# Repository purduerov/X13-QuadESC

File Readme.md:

# Readme for X13-QuadESC

Whenever you make a new part, download the datasheet and save it here _**and**_ with the part in the parts library

Always pull other people's changes before beginning to work
`git pull`

Be sure to push your changes after  working on them. Run:
1. `git add .` to add any files in this directory or a subdirectory
or `git add -u` to add any modified files
2. (Optional) `git clean -nX` to see what ignored files can be removed
	`git clean -fX` removes ignored files (Eagle backups)
3. `git commit -m "helpful commit message"` with a description of the work that you did
4. `git push` to push your work to github

Other helpful commands
* `git status` says information about modified and staged files
* `git log` shows the recent commits of the repository
* `git log filename.extension` show the recent commits for just that file
* `git checkout first-couple-letter-of-commit-id` lets you go back to a previous version
* `git checkout master` brings you back to the latest commit
* `git tag` lists the tags
* `git tag -a orderX -m "the version of the board placed for the X'th order"` tag a specific commit
* `git push --tags` needed to push tags to remote
* `git show orderX` show the commit log for the given tag
* `git checkout orderX` go back and interact with the files at the tagged commit

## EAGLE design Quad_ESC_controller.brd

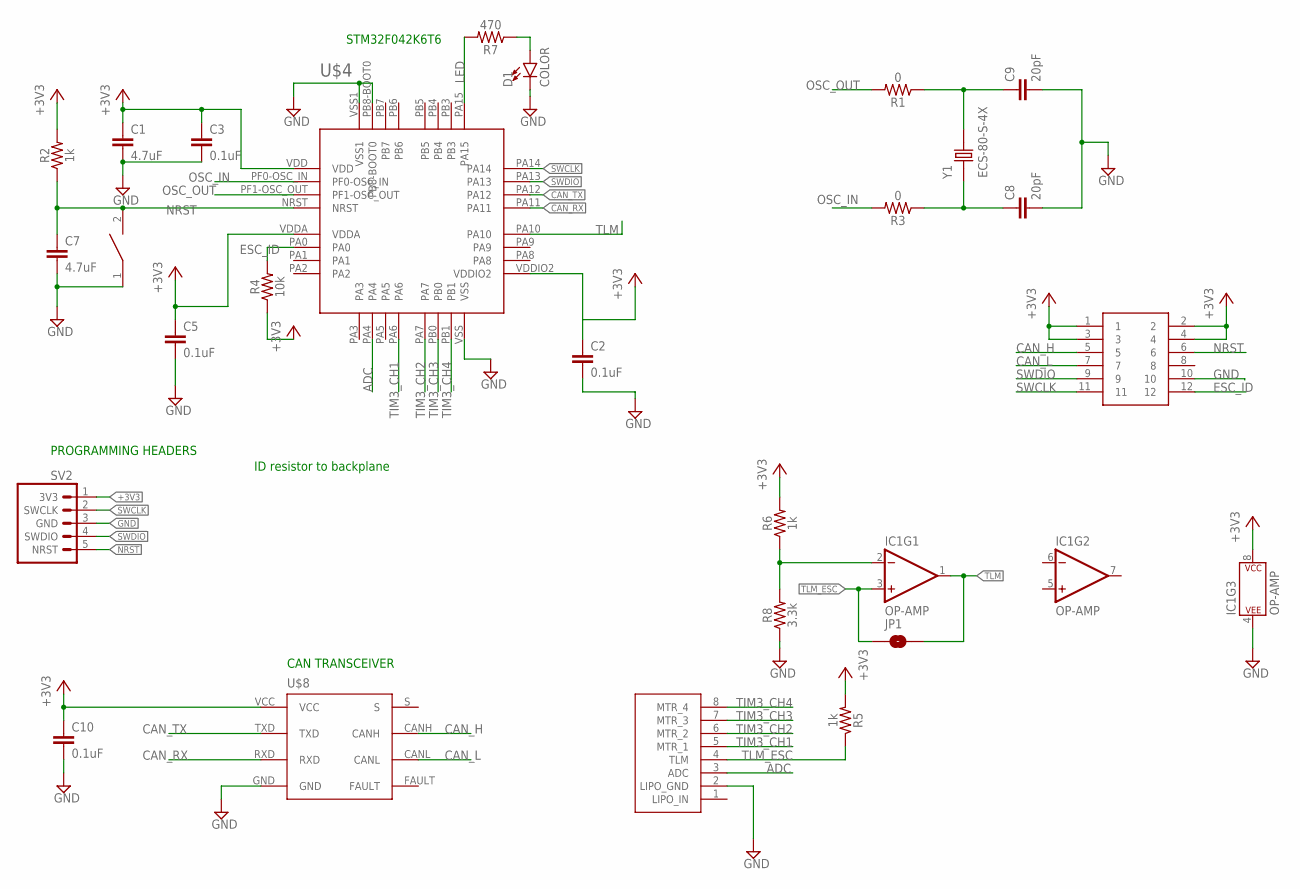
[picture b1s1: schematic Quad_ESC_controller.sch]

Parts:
C1, C7: 4.7uF; 0603
C2, C3, C5, C10: 0.1uF; 0603
C8, C9: 20pF; 0603
D1: COLOR; 0805
IC1: OP-AMP; SO08
JP1: JUMPER-SMT_2_NO_SILK; SMT-JUMPER_2_NO_SILK
R1, R3: 0; 0603
R2, R5, R6: 1k; 0603
R4: 10k; 0603
R7: 470; 0603
R8: 3.3k; 0603
RESET: DISCRETECOMPONENTS_SWITCH; DISCRETECOMPONENTS_SW_2512
SV2: 3V3 -SWCLK-GND-SWDIO- NRST; 1X05
U$2: JST-8PIN; 8PIN_CONNECTOR
U$3: BACKPLANE_CONNECTORSESC; BACKPLANE_CONNECTORS_ESC
U$4: STM32F042K6T6
U$8: TCAN337D
Y1: ECS-80-S-4X; XTAL_ECS-80-S-4X

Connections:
+3V3: C1.1, C2.1, C3.1, C5.1, C10.1, IC1.8 (P$V+), R2.2, R4.1, R5.2, R6.2, SV2.1 (3V3), U$3.1, U$3.2, U$3.3, U$3.4, U$4.VDD, U$4.VDDA, U$4.VDDIO2, U$8.VCC
ADC: U$2.3 (ADC), U$4.PA4
CAN_H: U$3.5, U$8.CANH
CAN_L: U$3.7, U$8.CANL
CAN_RX: U$4.PA11, U$8.RXD
CAN_TX: U$4.PA12, U$8.TXD
ESC_ID: R4.2, U$3.12, U$4.PA0
GND: C1.2, C2.2, C3.2, C5.2, C7.2, C8.2, C9.2, C10.2, D1.C, IC1.4 (P$V-), R8.1, RESET.1, SV2.3 (GND), U$2.2 (LIPO_GND), U$3.10, U$4.PB8-BOOT0, U$4.VSS, U$4.VSS1, U$8.GND
LED: R7.2, U$4.PA15
unnamed: C9.1, R1.1, Y1.2
unnamed: C8.1, R3.1, Y1.1
unnamed: IC1.2 (-IN), R6.1, R8.2
unnamed: D1.A, R7.1
NRST: C7.1, R2.1, RESET.2, SV2.5 (NRST), U$3.6, U$4.NRST
OSC_IN: R3.2, U$4.PF0-OSC_IN
OSC_OUT: R1.2, U$4.PF1-OSC_OUT
SWCLK: SV2.2 (SWCLK), U$3.11, U$4.PA14
SWDIO: SV2.4 (SWDIO), U$3.9, U$4.PA13
TIM3_CH1: U$2.5 (MTR_1), U$4.PA6
TIM3_CH2: U$2.6 (MTR_2), U$4.PA7
TIM3_CH3: U$2.7 (MTR_3), U$4.PB0
TIM3_CH4: U$2.8 (MTR_4), U$4.PB1
TLM: IC1.1 (OUT), JP1.2, U$4.PA10
TLM_ESC: IC1.3 (+IN), JP1.1, R5.1, U$2.4 (TLM)

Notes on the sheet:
STM32F042K6T6
PROGRAMMING HEADERS
CAN TRANSCEIVER
ID resistor to backplane

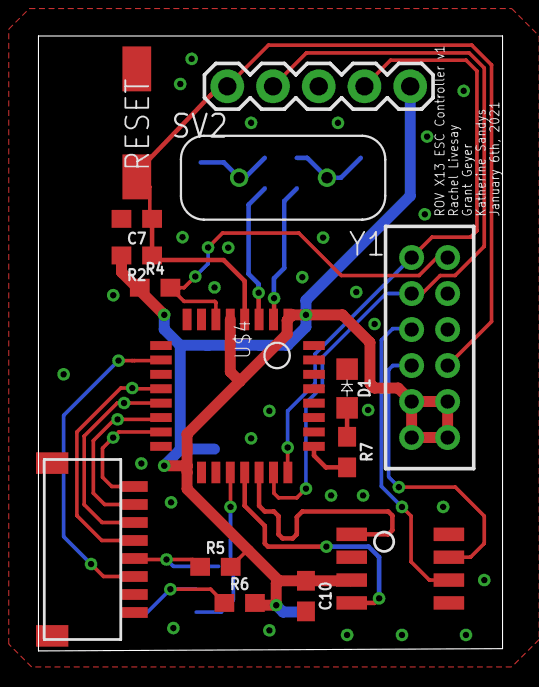
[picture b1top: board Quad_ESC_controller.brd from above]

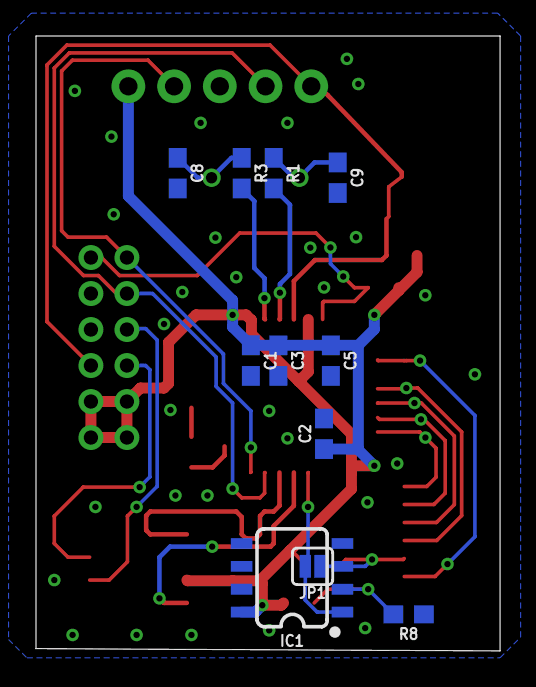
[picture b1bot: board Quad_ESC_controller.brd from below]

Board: 2 copper layers, 25.8 x 34.2 mm, 26 parts (11 on the bottom side), 24 nets.

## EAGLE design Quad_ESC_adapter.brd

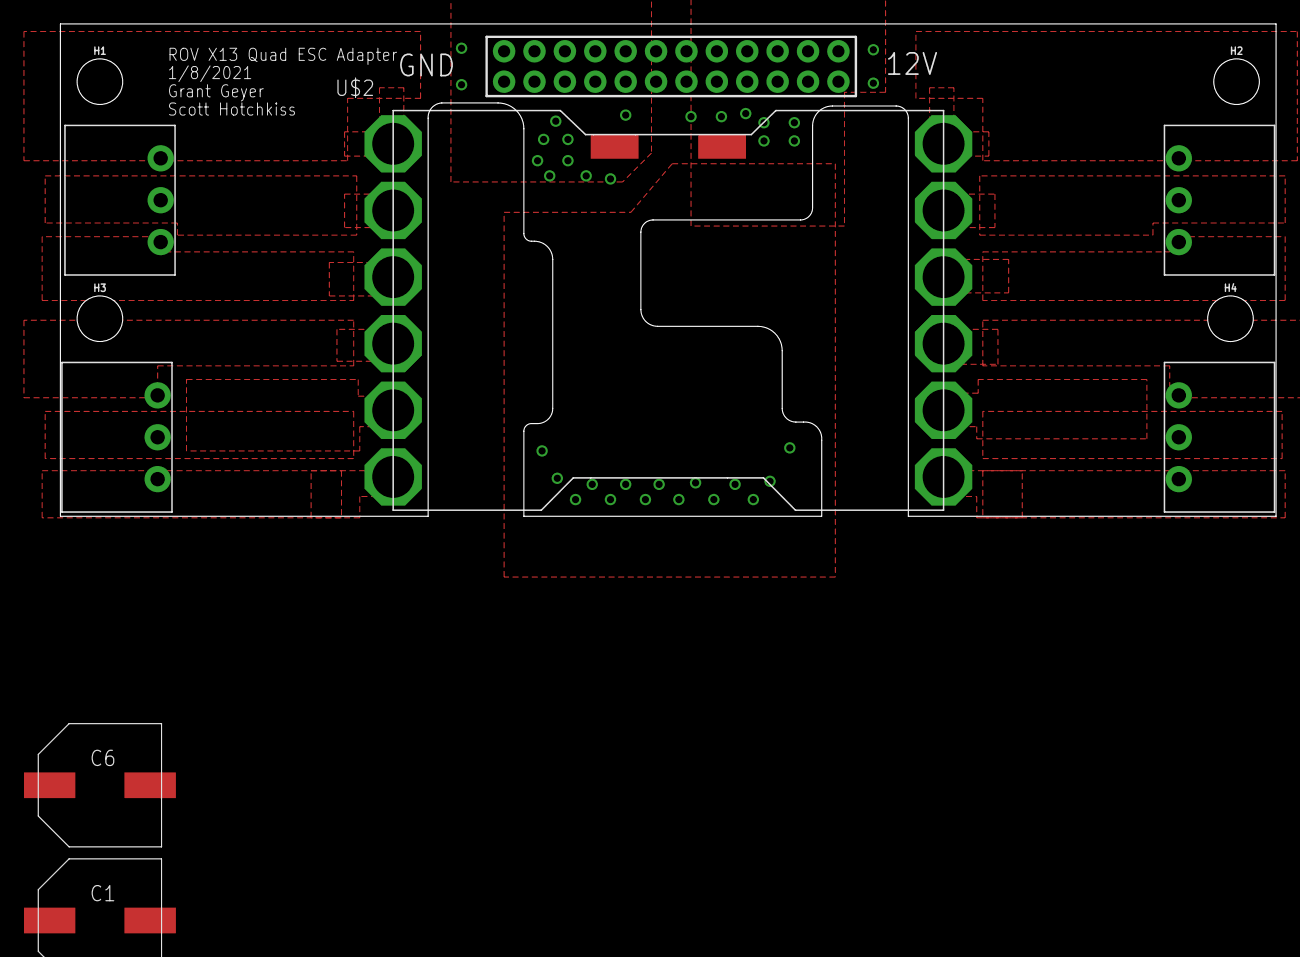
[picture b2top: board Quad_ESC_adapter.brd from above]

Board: 2 copper layers, 101.6 x 41.1 mm, 13 parts (1 on the bottom side), 14 nets, no tracks yet.

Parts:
C1, C5, C6: 330uF; CAPAE1030X1050N
H1, H2, H3, H4: 6-32-HOLE
J1, J2, J3, J4: 284512-3
U$2: BACKPLANE_ESC_ADAPTER_PWRESC; BACKPLANE_ESC_ADAPTER_ESC_PWR
U$10: LUMENIER_QUAD-NO-CUT

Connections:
12V: C1.+, C5.+, C6.+, U$2.12V@1, U$2.12V@2, U$2.12V@3, U$2.12V@4, U$2.12V@5, U$2.12V@6, U$2.12V@7, U$2.12V@8, U$2.12V@9, U$2.12V@10, U$2.12V@11, U$2.12V@12, U$10.VIN
ESC1_B: J1.3, U$10.1
ESC1_R: J1.1, U$10.3
ESC1_Y: J1.2, U$10.2
ESC2_B: J2.3, U$10.4
ESC2_R: J2.1, U$10.6
ESC2_Y: J2.2, U$10.5
ESC3_B: J3.1, U$10.12
ESC3_R: J3.3, U$10.10
ESC3_Y: J3.2, U$10.11
ESC4_B: J4.1, U$10.9
ESC4_R: J4.3, U$10.7
ESC4_Y: J4.2, U$10.8
GND: C1.-, C5.-, C6.-, U$2.GND@1, U$2.GND@2, U$2.GND@3, U$2.GND@4, U$2.GND@5, U$2.GND@6, U$2.GND@7, U$2.GND@8, U$2.GND@9, U$2.GND@10, U$2.GND@11, U$2.GND@12, U$10.GND

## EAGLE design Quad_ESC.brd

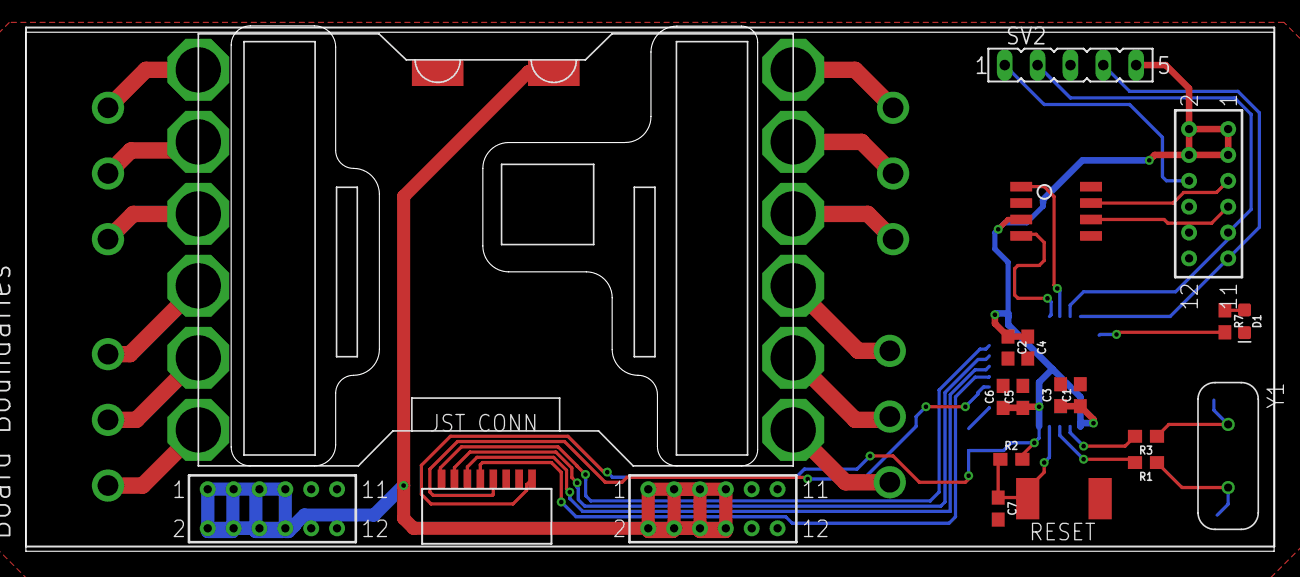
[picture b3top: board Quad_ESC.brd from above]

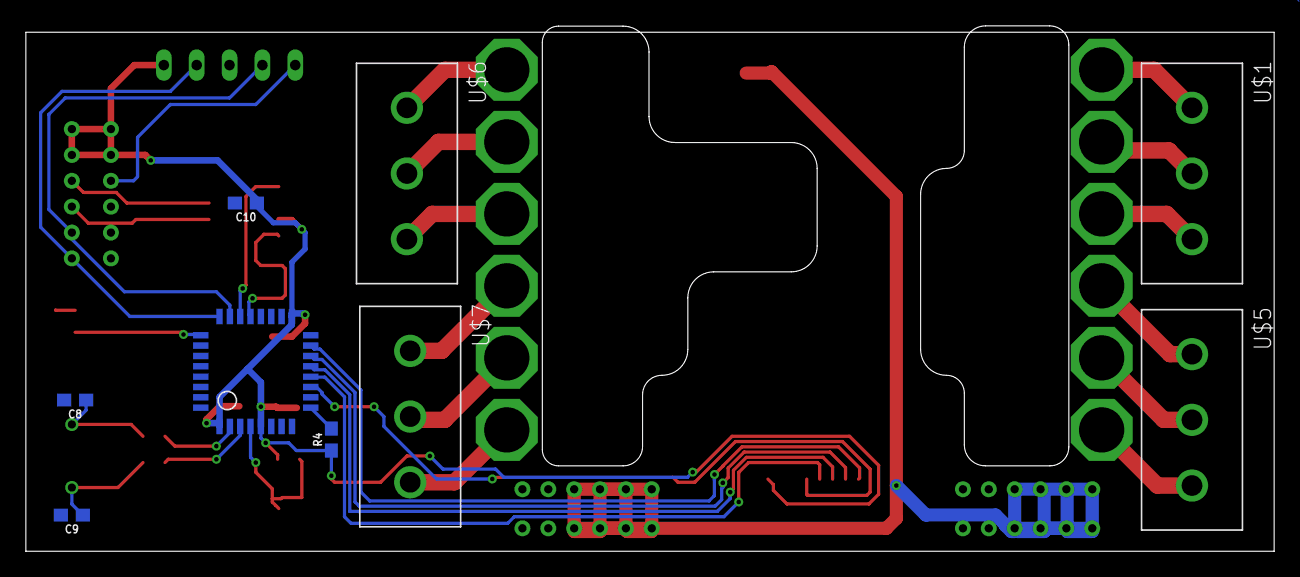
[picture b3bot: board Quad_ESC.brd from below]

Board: 2 copper layers, 96.5 x 40.1 mm, 28 parts (9 on the bottom side), 35 nets.

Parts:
C1, C2, C3, C4, C5, C6, C7, C8, C9: 4.7uF; 0603
C10: 100nF; 0603
D1: LED-0603
R1, R2, R3: 1k; 0603
R4: 10k; 0603
R7: 0603
RESET: SW_2512
SV2: FE05-1
U$1, U$5, U$6, U$7: 3PINCONNECTOR
U$2: 8PIN_CONNECTOR; 8PI_CONNECTOR
U$3: BACKPLANE_CONNECTORS
U$4: STM32F042K6T6
U$8: TCAN337D
U$10: LUMENIER_QUAD
Y1: ECS-80-S-4X; XTAL_ECS-80-S-4X

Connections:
+3V3: C1.1, C2.1, C3.1, C4.1, C5.1, C6.1, C10.1, R2.2, R4.1, SV2.5, U$2.P$1, U$3.25, U$3.26, U$3.27, U$3.28, U$4.VDD, U$4.VDDA, U$4.VDDIO2, U$8.VCC
+12V: U$3.1, U$3.2, U$3.3, U$3.4, U$3.5, U$3.6, U$3.7, U$3.8, U$3.13, U$3.14, U$3.15, U$3.16, U$3.17, U$3.18, U$3.19, U$3.20, U$10.VIN
CAN_H: U$3.29, U$8.CANH
CAN_L: U$3.31, U$8.CANL
CAN_RX: U$4.PA11, U$8.RXD
CAN_TX: U$4.PA12, U$8.TXD
ESC1_B: U$1.A, U$10.1
ESC1_R: U$1.C, U$10.3
ESC1_Y: U$1.B, U$10.2
ESC2_B: U$5.A, U$10.4
ESC2_R: U$5.C, U$10.6
ESC2_Y: U$5.B, U$10.5
ESC3_B: U$6.A, U$10.12
ESC3_R: U$6.C, U$10.10
ESC3_Y: U$6.B, U$10.11
ESC4_B: U$7.A, U$10.9
ESC4_R: U$7.C, U$10.7
ESC4_Y: U$7.B, U$10.8
GND: C1.2, C2.2, C3.2, C4.2, C5.2, C6.2, C7.2, C8.2, C9.2, C10.2, D1.C, RESET.1, SV2.3, U$2.P$2, U$2.P$3, U$3.9, U$3.10, U$3.11, U$3.12, U$3.21, U$3.22, U$3.23, U$3.24, U$4.PB8-BOOT0, U$4.VSS, U$4.VSS1, U$8.GND, U$10.GND
LED: R7.2, U$4.PA15
unnamed: C9.1, R1.1, Y1.2
unnamed: C8.1, R3.1, Y1.1
unnamed: R4.2, U$4.PA3
unnamed: D1.A, R7.1
NRST: SV2.1, U$3.30
NRST1: C7.1, R2.1, RESET.2, U$4.NRST
OSC_IN: R3.2, U$4.PF0-OSC_IN
OSC_OUT: R1.2, U$4.PF1-OSC_OUT
SWCLK: SV2.4, U$3.35, U$4.PA14
SWDIO: SV2.2, U$3.33, U$4.PA13
TIM3_CH1: U$2.P$5, U$4.PA6
TIM3_CH2: U$2.P$6, U$4.PA7
TIM3_CH3: U$2.P$7, U$4.PB0
TIM3_CH4: U$2.P$8, U$4.PB1
TLM: U$2.P$4, U$4.PA5

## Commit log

2020-09-18 setup of repo
2020-10-10 Create Quad_ESC.sch
    created file, moved over parts from X12 version
2020-10-17 Lib Changes/Schem Update
    Added Cutouts/changed dimensions of ESC footprint in library; added board parts to library; tweaked schematic; created board file.
2020-10-17 Lib Update (again)
    ok definitely did not push the wrong version of the library file last time haha
2020-10-17 Lib Update/Sch Update
    Migrated 3 pin connectors from X-11 AFRO lib; fixed BLHeli symbol so labels no longer overlap; fixed connections and placement on schematic.
2020-10-21 Board Update
    Added minor pin connections
2020-10-24 Lib/Schem Update
    tweaked connections to STM chip; split esc device into lumenier ESC and 8 pin connector (need to figure out how to pair those still :/ ); scooted around components on schematic
2020-10-25 turn off layer 93 (pins). Create correct dimension board
2020-10-27 made board a little smaller
2020-11-12 Schem/Lib Update
    added new footprint to schematic and library, added ID resistor to chip, standardized symbols across schematic
2020-11-14 Minor Sch Fixes/Board Placement
    Fixed issues with schematic and doubling of backplane connectors, precursory board placements and connections
2020-11-14 Quick Board Update
    ripup; done for presentation, only placement of components present on board
2020-11-21 Board/Schem Update
    added CLT low profile samtec connectors to schem/board, looking at the connector spacing on the board stresses me out ;-;
2020-11-21 Board Update
    actually put the connectors on the right side of the board this time haha
2020-12-02 Connector Update!!
    made new part for backplae connectors with proper spacing, updated schematic and board accordingly
2020-12-03 Update BLHeli_32 45A.lbr
    Added boundary box to connectors part for backplane.
2020-12-06 Connector Updates, Board Routing
    Backplane connectors updated, board routing on right side completed
2020-12-06 Signals fixed a bit?
2020-12-06 Board Update (again)
2020-12-06 Quick, Minor Changes
2021-01-03 remove lumenier and adjust size for controller
2021-01-03 split into adapter board
2021-01-04 complete connector placement
2021-01-05 Export step file
2021-01-06 Placement/Routing Update
    the board and sch are out of sync and i have no idea how they got that way h e l p
2021-01-06 tented vias under lumenier
2021-01-06 routed wider board
2021-01-07 Placement/Routing Update
    microcontroller movied to front, CAN signals length checked
2021-01-07 Small Board Change
    forgot to trace length check the OSC in/out oops
2021-01-07 Library Changes for Backplane :)
2021-01-07 Routing Update
    rerouted new connector into board :)
2021-01-07 Labels/Final Touches
    Added: Vias, Names/Date/Board Label, Kingsman Logo :D
2021-01-08 routed with 2x12 block. Basically ready to order
2021-01-09 single outline version
2021-01-09 this has been the best graphic in the history of graphics, maybe ever
2021-01-10 Final Board Changes ✽-(ˆ▿ˆ)/✽
    thank god
    (changes: vias con. to GND, esc id/tlm connections, design moved, connector footprint replaced, font sizes changed)
2021-01-10 JST part
2021-01-10 exports for ordering
2021-01-11 Final Board Changes Pt. 2: Electric Boogaloo
    Changes: [ bumped out board 100mil to the left, flipped esc signals on micro, moved TLM to analog pin 10 on micro, rotated connector, and rerouted board. ]
2021-01-11 re print schematic for controller
2021-01-25 Use new JST footprint with mechanical solder pads (for future reference/v2)
2021-02-07 Labels on adapter board and enlarge cutout
2021-02-10 Added 1k Resistor TLM -> 3.3V
    also tried airwiring it lol. it's v bad, but that is next year's problem.
2021-03-06 Library/Board Update
    Added t-stop to pads on esc connector :)
2021-05-09 Add op amp for telemetry logic level fixing
2021-05-24 New SWD programming connector
2021-08-12 Use aluminum caps for the adapter board

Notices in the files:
parts and their libraries:
SparkFun-Capacitors: Licensing: Creative Commons ShareAlike 4.0 International - https://creativecommons.org/licenses/by-sa/4.0
